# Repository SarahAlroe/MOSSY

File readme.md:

_Work in progress_  
# MOSSY  
A collection sound synthesis and processing electronics and software. 
_Work in progress_

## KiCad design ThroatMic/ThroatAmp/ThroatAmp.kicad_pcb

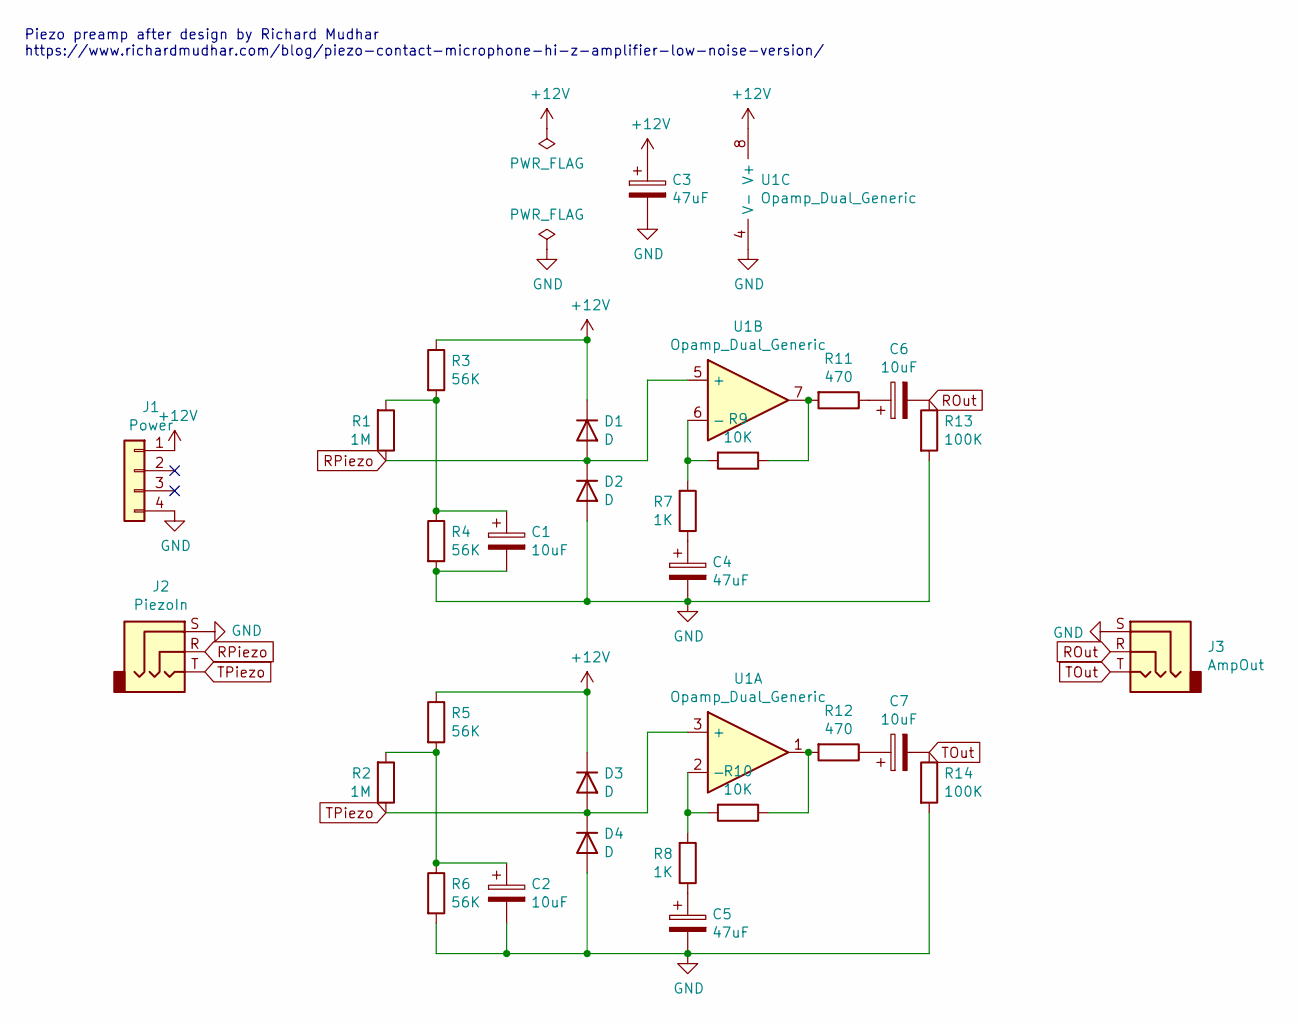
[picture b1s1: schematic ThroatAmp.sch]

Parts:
C1, C2, C6, C7: 10uF; C_Disc_D4.7mm_W2.5mm_P5.00mm
C3, C4, C5: 47uF; C_Disc_D4.7mm_W2.5mm_P5.00mm
D1, D2, D3, D4: D; D_5W_P10.16mm_Horizontal
J1: Power; PinHeader_1x04_P2.54mm_Horizontal
J2: PiezoIn; Jack_3.5mm_CUI_SJ1-3533NG_Horizontal
J3: AmpOut; Jack_3.5mm_CUI_SJ1-3533NG_Horizontal
R1, R2: 1M; R_Axial_DIN0207_L6.3mm_D2.5mm_P10.16mm_Horizontal
R3, R4, R5, R6: 56K; R_Axial_DIN0207_L6.3mm_D2.5mm_P10.16mm_Horizontal
R7, R8: 1K; R_Axial_DIN0207_L6.3mm_D2.5mm_P10.16mm_Horizontal
R9, R10: 10K; R_Axial_DIN0207_L6.3mm_D2.5mm_P10.16mm_Horizontal
R11, R12: 470; R_Axial_DIN0207_L6.3mm_D2.5mm_P10.16mm_Horizontal
R13, R14: 100K; R_Axial_DIN0207_L6.3mm_D2.5mm_P10.16mm_Horizontal
U1: Opamp_Dual_Generic; DIP-8_W7.62mm_LongPads

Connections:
+12V: C3.1, D1.1 (K), D3.1 (K), J1.1, R3.1, R5.1, U1.8 (V+)
GND: C1.2, C2.2, C3.2, C4.2, C5.2, D2.2 (A), D4.2 (A), J1.4, J2.S, J3.S, R4.2, R6.2, R13.2, R14.2, U1.4 (V-)
unnamed: C1.1, R1.2, R3.2, R4.1
unnamed: C2.1, R2.2, R5.2, R6.1
unnamed: C4.1, R7.1
unnamed: C5.1, R8.1
unnamed: C6.1, R11.1
unnamed: C7.1, R12.1
unnamed: R7.2, R9.2, U1.6 (-)
unnamed: R10.1, R12.2, U1.1
unnamed: R8.2, R10.2, U1.2 (-)
unnamed: R9.1, R11.2, U1.7
ROut: C6.2, J3.R, R13.1
RPiezo: D1.2 (A), D2.1 (K), J2.R, R1.1, U1.5 (+)
TOut: C7.2, J3.T, R14.1
TPiezo: D3.2 (A), D4.1 (K), J2.T, R2.1, U1.3 (+)

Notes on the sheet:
Piezo preamp after design by Richard Mudhar https://www.richardmudhar.com/blog/piezo-contact-microphone-hi-z-amplifier-low-noise-version/

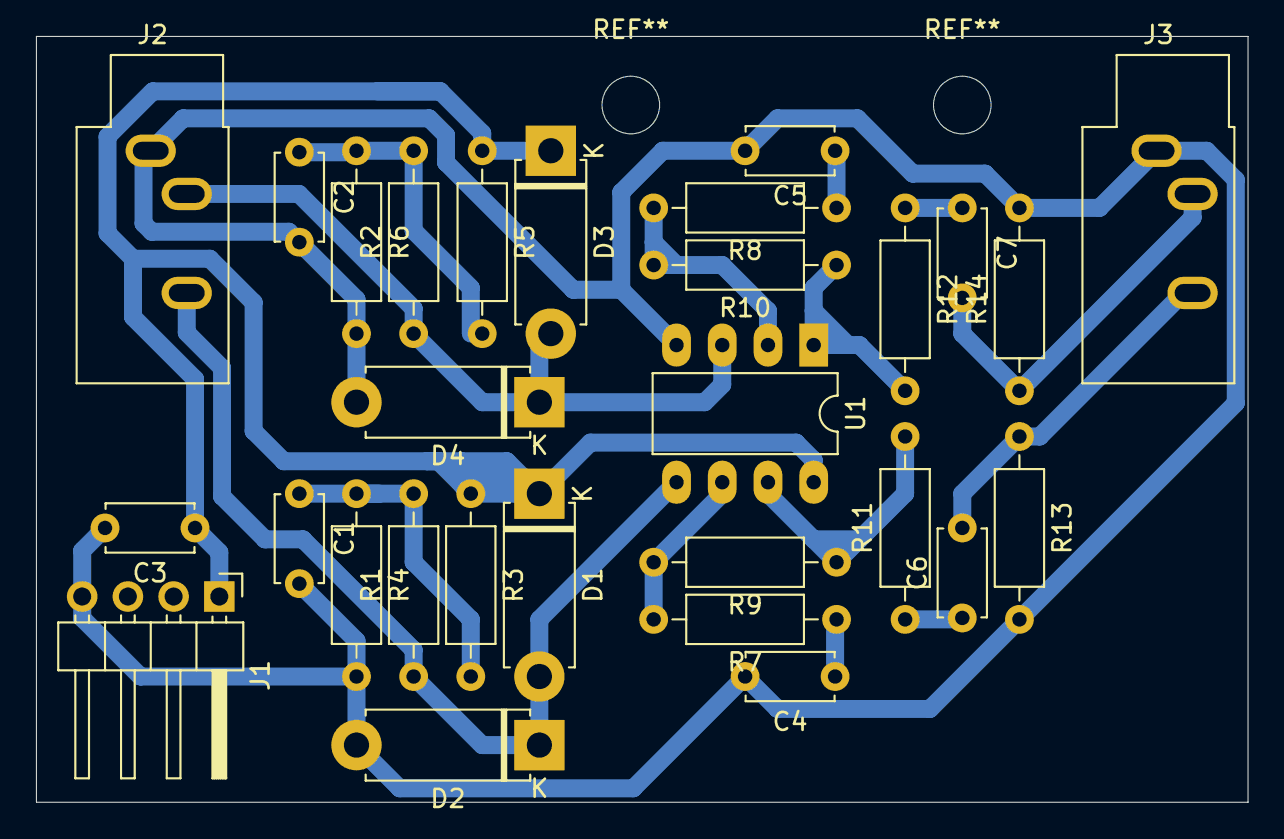
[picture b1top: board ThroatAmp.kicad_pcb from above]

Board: 2 copper layers, 67.3 x 42.5 mm, 29 parts (0 on the bottom side), 16 nets.

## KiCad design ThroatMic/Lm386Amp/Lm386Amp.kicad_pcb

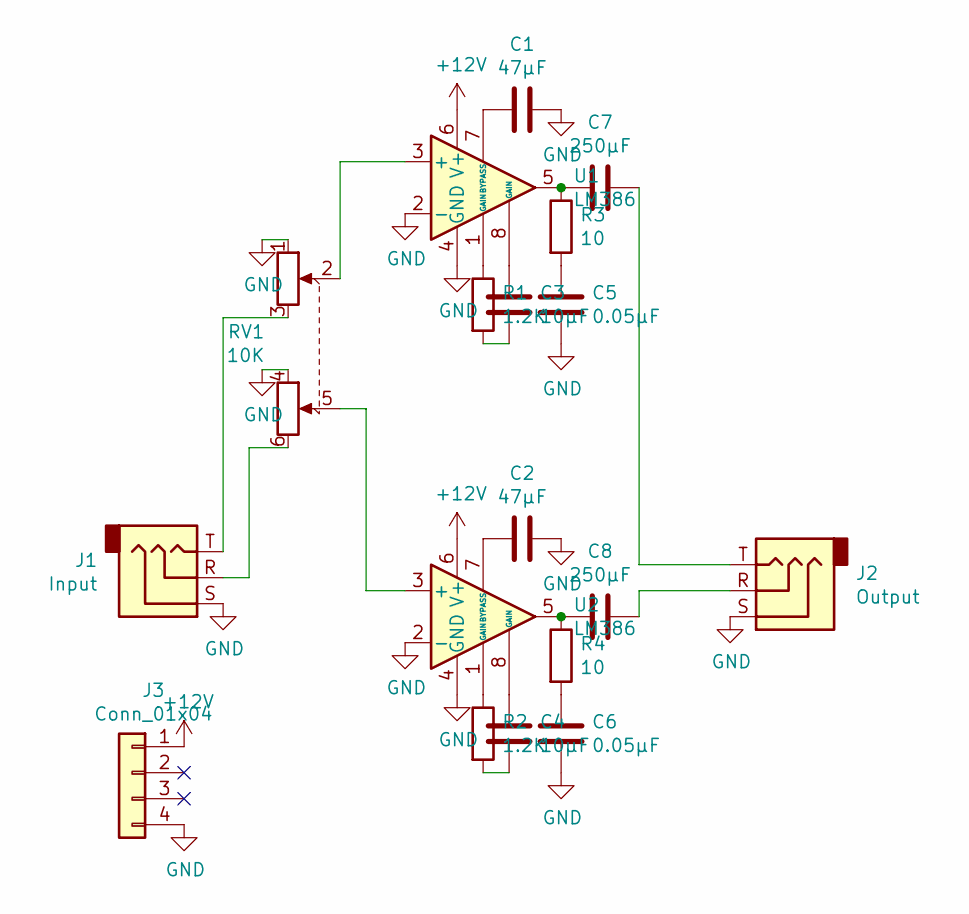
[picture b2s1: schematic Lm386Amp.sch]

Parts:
C1, C2: 47µF; C_Disc_D4.7mm_W2.5mm_P5.00mm
C3, C4: 10µF; C_Disc_D4.7mm_W2.5mm_P5.00mm
C5, C6: 0.05µF; C_Disc_D4.7mm_W2.5mm_P5.00mm
C7, C8: 250µF; C_Disc_D4.7mm_W2.5mm_P5.00mm
J1: Input; Jack_3.5mm_CUI_SJ1-3533NG_Horizontal
J2: Output; Jack_3.5mm_CUI_SJ1-3533NG_Horizontal
J3: Conn_01x04; PinHeader_1x04_P2.54mm_Horizontal
R1, R2: 1.2K; R_Axial_DIN0207_L6.3mm_D2.5mm_P10.16mm_Horizontal
R3, R4: 10; R_Axial_DIN0207_L6.3mm_D2.5mm_P10.16mm_Horizontal
RV1: 10K; Potentiometer_Alps_RK163_Dual_Horizontal
U1, U2: LM386; DIP-8_W7.62mm_Socket_LongPads

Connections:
+12V: J3.1, U1.6 (V+), U2.6 (V+)
GND: C1.2, C2.2, C5.2, C6.2, J1.S, J2.S, J3.4, RV1.1, RV1.4, U1.2 (-), U1.4 (GND), U2.2 (-), U2.4 (GND)
unnamed: C1.1, U1.7 (BYPASS)
unnamed: C2.1, U2.7 (BYPASS)
unnamed: C3.1, U1.8 (GAIN)
unnamed: C3.2, R1.2
unnamed: C4.1, U2.8 (GAIN)
unnamed: C4.2, R2.2
unnamed: C5.1, R3.2
unnamed: C6.1, R4.2
unnamed: C7.1, J2.T
unnamed: C7.2, R3.1, U1.5
unnamed: C8.1, J2.R
unnamed: C8.2, R4.1, U2.5
unnamed: J1.R, RV1.6
unnamed: J1.T, RV1.3
unnamed: R1.1, U1.1 (GAIN)
unnamed: R2.1, U2.1 (GAIN)
unnamed: RV1.2, U1.3 (+)
unnamed: RV1.5, U2.3 (+)

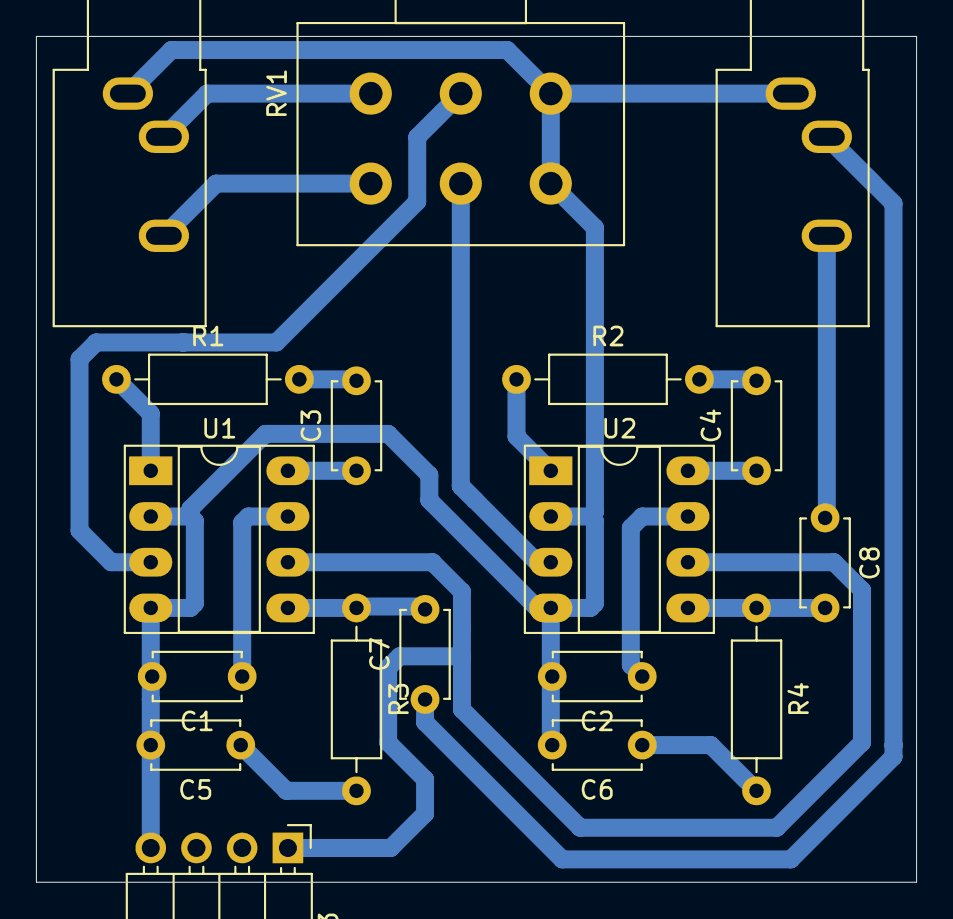
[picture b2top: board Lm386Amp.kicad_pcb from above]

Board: 2 copper layers, 48.9 x 47.0 mm, 18 parts (0 on the bottom side), 20 nets.

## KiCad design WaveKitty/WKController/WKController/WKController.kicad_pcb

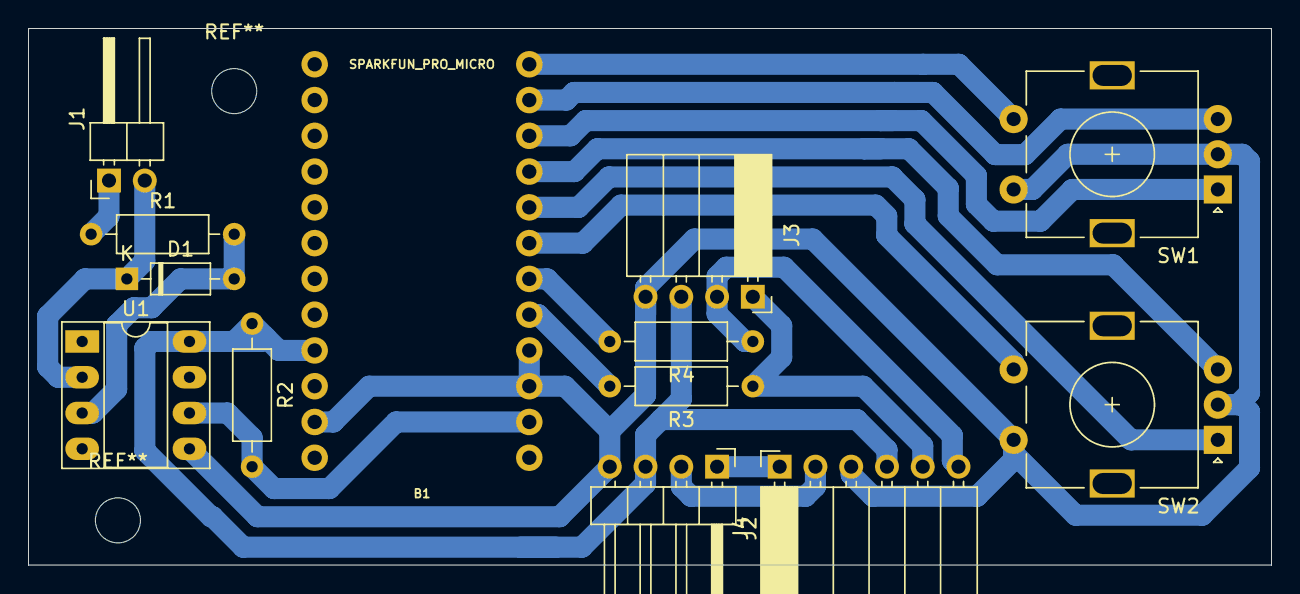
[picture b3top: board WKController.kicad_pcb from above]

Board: 2 copper layers, 88.3 x 38.1 mm, 13 parts (0 on the bottom side), 18 nets.

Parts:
B1: SPARKFUN_PRO_MICRO
D1: 1N914; D_DO-35_SOD27_P7.62mm_Horizontal
J1: MIDI; PinHeader_1x02_P2.54mm_Horizontal
J2: Power; PinHeader_1x04_P2.54mm_Horizontal
J3: SSD1306; PinSocket_1x04_P2.54mm_Horizontal
J4: VoiceCon; PinSocket_1x06_P2.54mm_Horizontal
R1: 220; R_Axial_DIN0207_L6.3mm_D2.5mm_P10.16mm_Horizontal
R2: 270; R_Axial_DIN0207_L6.3mm_D2.5mm_P10.16mm_Horizontal
R3, R4: 0; R_Axial_DIN0207_L6.3mm_D2.5mm_P10.16mm_Horizontal
SW1: L_ENC; RotaryEncoder_Alps_EC11E-Switch_Vertical_H20mm
SW2: R_ENC; RotaryEncoder_Alps_EC11E-Switch_Vertical_H20mm
U1: 6N138; DIP-8_W7.62mm_Socket_LongPads

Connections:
+5V: B1.21, J2.3, J3.3, J4.4, R2.1, U1.8
+12V: J2.1, J4.1
-12V: J2.2, J4.2
GND: B1.3, B1.4, B1.23, J2.4, J3.4, J4.3, SW1.C, SW1.S2, SW2.C, SW2.S2, U1.5
L_ENC_A: B1.10, SW1.A
L_ENC_B: B1.11, SW1.B
L_ENC_S: B1.12, SW1.S1
unnamed: B1.5, R3.2
unnamed: B1.6, R4.2
unnamed: D1.1, J1.2, U1.2
unnamed: D1.2, R1.2, U1.3
unnamed: J1.1, R1.1
RXI: B1.2, R2.2, U1.6
R_ENC_A: B1.8, SW2.A
R_ENC_B: B1.9, SW2.B
R_ENC_S: B1.7, SW2.S1
SCL: J3.2, J4.6, R4.1
SDA: J3.1, J4.5, R3.1

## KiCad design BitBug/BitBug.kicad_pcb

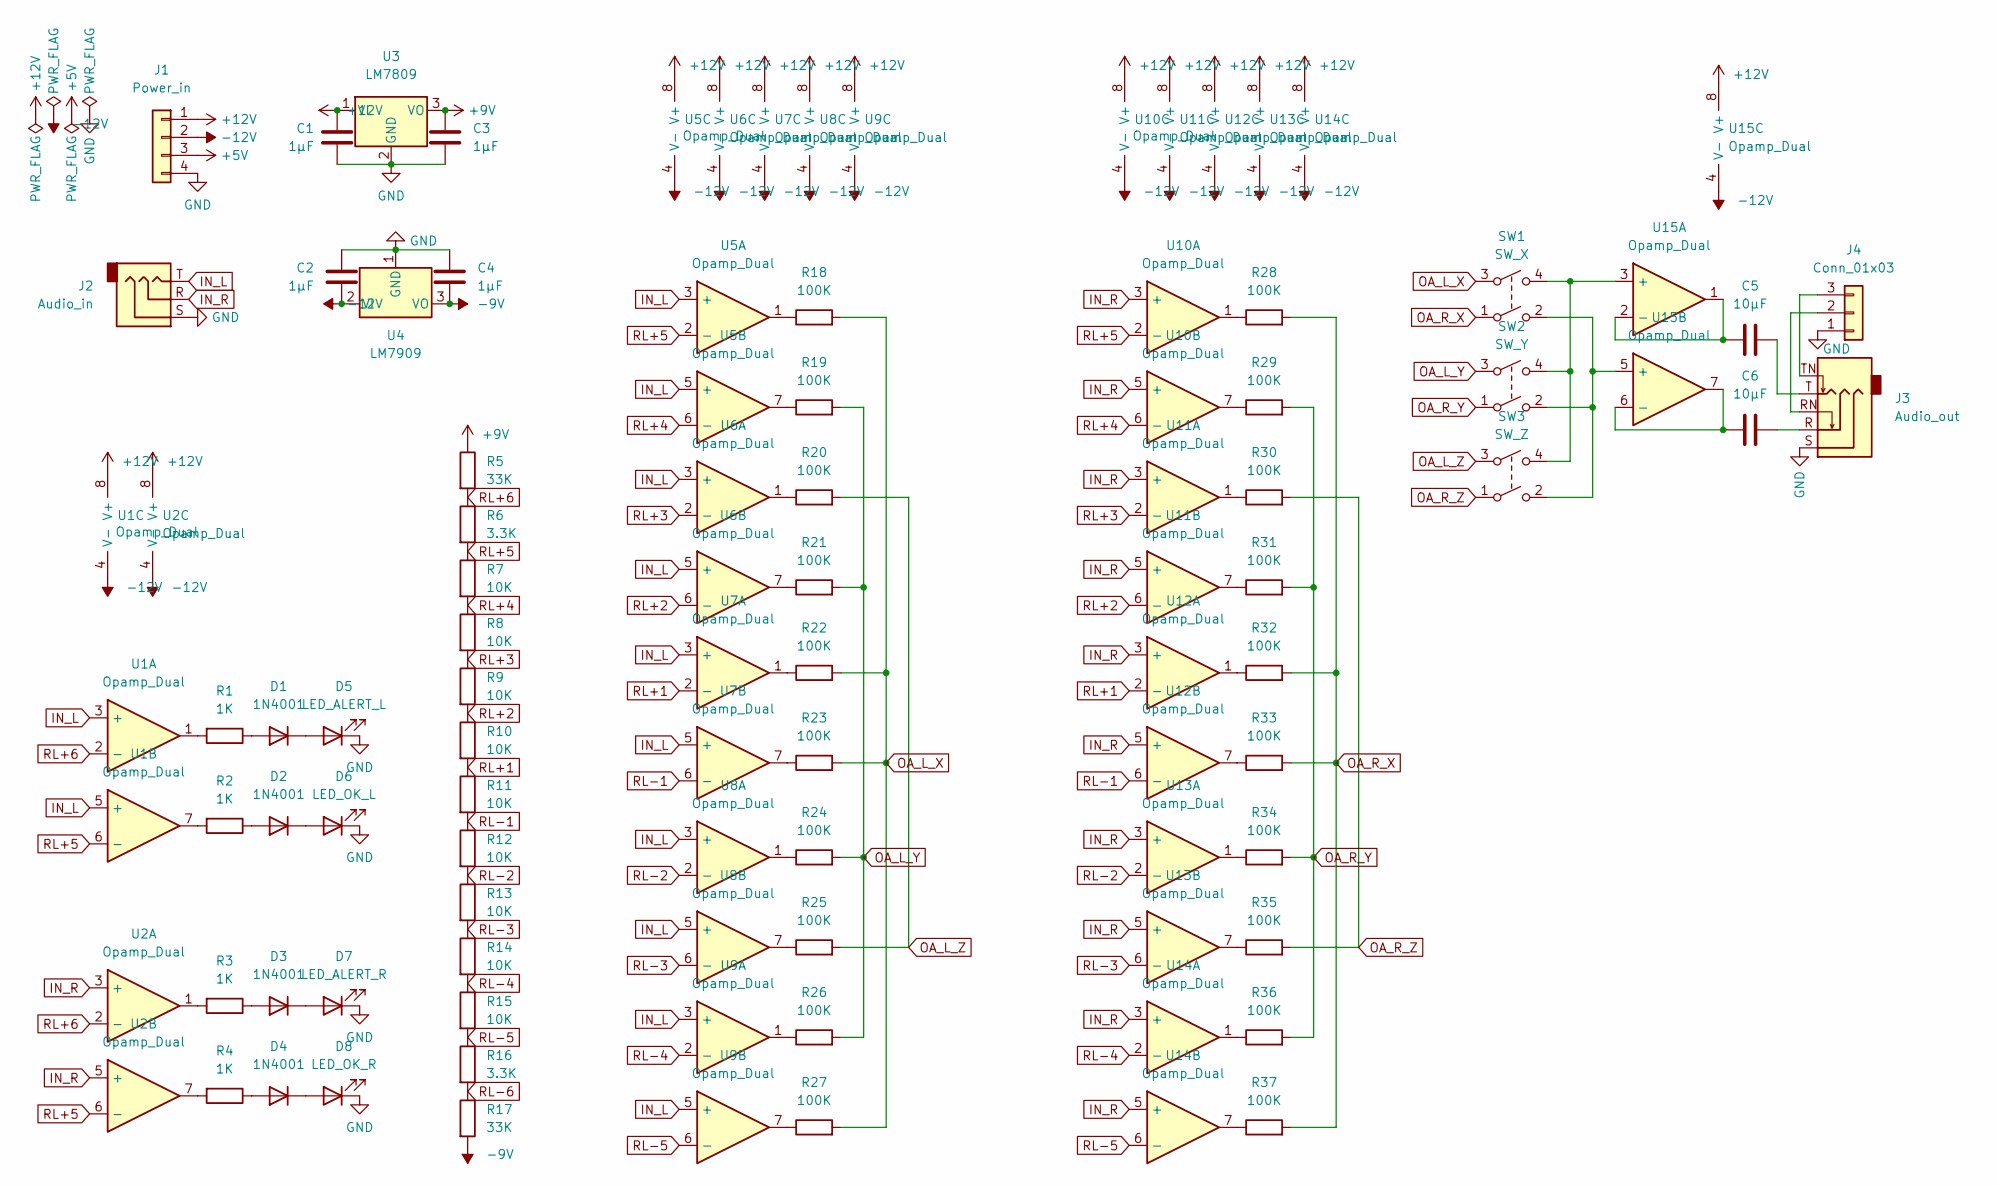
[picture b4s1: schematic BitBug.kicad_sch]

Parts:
C1, C2, C3, C4: 1µF; C_Disc_D4.7mm_W2.5mm_P5.00mm
C5, C6: 10µF; C_Disc_D4.7mm_W2.5mm_P5.00mm
D1, D2, D3, D4: 1N4001; D_DO-41_SOD81_P10.16mm_Horizontal
D5: LED_ALERT_L; LED_D5.0mm
D6: LED_OK_L; LED_D5.0mm
D7: LED_ALERT_R; LED_D5.0mm
D8: LED_OK_R; LED_D5.0mm
J1: Power_in; PinHeader_1x04_P2.54mm_Horizontal
J2: Audio_in; Jack_3.5mm_Ledino_KB3SPRS_Horizontal
J3: Audio_out; Jack_3.5mm_Ledino_KB3SPRS_Horizontal
J4: Conn_01x03; PinSocket_1x03_P2.54mm_Vertical
R1, R2, R3, R4: 1K; R_Axial_DIN0207_L6.3mm_D2.5mm_P7.62mm_Horizontal
R5, R17: 33K; R_Axial_DIN0207_L6.3mm_D2.5mm_P7.62mm_Horizontal
R6, R16: 3.3K; R_Axial_DIN0207_L6.3mm_D2.5mm_P7.62mm_Horizontal
R7, R8, R9, R10, R11, R12, R13, R14, R15: 10K; R_Axial_DIN0207_L6.3mm_D2.5mm_P7.62mm_Horizontal
R18, R19, R20, R21, R22, R23, R24, R25, R26, R27, R28, R29, R30, R31, R32, R33, R34, R35, R36, R37: 100K; R_Axial_DIN0207_L6.3mm_D2.5mm_P7.62mm_Horizontal
SW1: SW_X; PinSocket_1x04_P2.54mm_Vertical
SW2: SW_Y; PinSocket_1x04_P2.54mm_Vertical
SW3: SW_Z; PinSocket_1x04_P2.54mm_Vertical
U1, U2, U5, U6, U7, U8, U9, U10, U11, U12, U13, U14, U15: Opamp_Dual; DIP-8_W7.62mm_LongPads
U3: LM7809; TO-220-3_Vertical
U4: LM7909; TO-220-3_Vertical

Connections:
+5V: J1.3
+9V: C3.1, R5.1, U3.3 (VO)
+12V: C1.2, J1.1, U1.8 (V+), U2.8 (V+), U3.1 (VI), U5.8 (V+), U6.8 (V+), U7.8 (V+), U8.8 (V+), U9.8 (V+), U10.8 (V+), U11.8 (V+), U12.8 (V+), U13.8 (V+), U14.8 (V+), U15.8 (V+)
-9V: C4.2, R17.2, U4.3 (VO)
-12V: C2.1, J1.2, U1.4 (V-), U2.4 (V-), U4.2 (VI), U5.4 (V-), U6.4 (V-), U7.4 (V-), U8.4 (V-), U9.4 (V-), U10.4 (V-), U11.4 (V-), U12.4 (V-), U13.4 (V-), U14.4 (V-), U15.4 (V-)
GND: C1.1, C2.2, C3.2, C4.1, D5.1 (K), D6.1 (K), D7.1 (K), D8.1 (K), J1.4, J2.S, J3.S, J4.1, U3.2 (GND), U4.1 (GND)
IN_L: J2.T, U1.3 (+), U1.5 (+), U5.3 (+), U5.5 (+), U6.3 (+), U6.5 (+), U7.3 (+), U7.5 (+), U8.3 (+), U8.5 (+), U9.3 (+), U9.5 (+)
IN_R: J2.R, U2.3 (+), U2.5 (+), U10.3 (+), U10.5 (+), U11.3 (+), U11.5 (+), U12.3 (+), U12.5 (+), U13.3 (+), U13.5 (+), U14.3 (+), U14.5 (+)
unnamed: C5.1, U15.1, U15.2 (-)
unnamed: C5.2, J3.T
unnamed: C6.1, U15.6 (-), U15.7
unnamed: C6.2, J3.R
unnamed: D1.1 (K), D5.2 (A)
unnamed: D1.2 (A), R1.1
unnamed: D2.1 (K), D6.2 (A)
unnamed: D2.2 (A), R2.1
unnamed: D3.1 (K), D7.2 (A)
unnamed: D3.2 (A), R3.1
unnamed: D4.1 (K), D8.2 (A)
unnamed: D4.2 (A), R4.1
unnamed: J3.RN, J4.2
unnamed: J3.TN, J4.3
unnamed: R1.2, U1.1
unnamed: R2.2, U1.7
unnamed: R3.2, U2.1
unnamed: R4.2, U2.7
unnamed: R18.1, U5.1
unnamed: R19.1, U5.7
unnamed: R20.1, U6.1
unnamed: R21.1, U6.7
unnamed: R22.1, U7.1
unnamed: R23.1, U7.7
unnamed: R24.1, U8.1
unnamed: R25.1, U8.7
unnamed: R26.1, U9.1
unnamed: R27.1, U9.7
unnamed: R28.1, U10.1
unnamed: R29.1, U10.7
unnamed: R30.1, U11.1
unnamed: R31.1, U11.7
unnamed: R32.1, U12.1
unnamed: R33.1, U12.7
unnamed: R34.1, U13.1
unnamed: R35.1, U13.7
unnamed: R36.1, U14.1
unnamed: R37.1, U14.7
unnamed: SW1.2, SW2.2, SW3.2, U15.5 (+)
unnamed: SW1.4, SW2.4, SW3.4, U15.3 (+)
OA_L_X: R18.2, R22.2, R23.2, R27.2, SW1.3
OA_L_Y: R19.2, R21.2, R24.2, R26.2, SW2.3
OA_L_Z: R20.2, R25.2, SW3.3
OA_R_X: R28.2, R32.2, R33.2, R37.2, SW1.1
OA_R_Y: R29.2, R31.2, R34.2, R36.2, SW2.1
OA_R_Z: R30.2, R35.2, SW3.1
RL+1: R10.2, R11.1, U7.2 (-), U12.2 (-)
RL+2: R9.2, R10.1, U6.6 (-), U11.6 (-)
RL+3: R8.2, R9.1, U6.2 (-), U11.2 (-)
RL+4: R7.2, R8.1, U5.6 (-), U10.6 (-)
RL+5: R6.2, R7.1, U1.6 (-), U2.6 (-), U5.2 (-), U10.2 (-)
RL+6: R5.2, R6.1, U1.2 (-), U2.2 (-)
RL-1: R11.2, R12.1, U7.6 (-), U12.6 (-)
RL-2: R12.2, R13.1, U8.2 (-), U13.2 (-)
RL-3: R13.2, R14.1, U8.6 (-), U13.6 (-)
RL-4: R14.2, R15.1, U9.2 (-), U14.2 (-)
RL-5: R15.2, R16.1, U9.6 (-), U14.6 (-)
RL-6: R16.2, R17.1

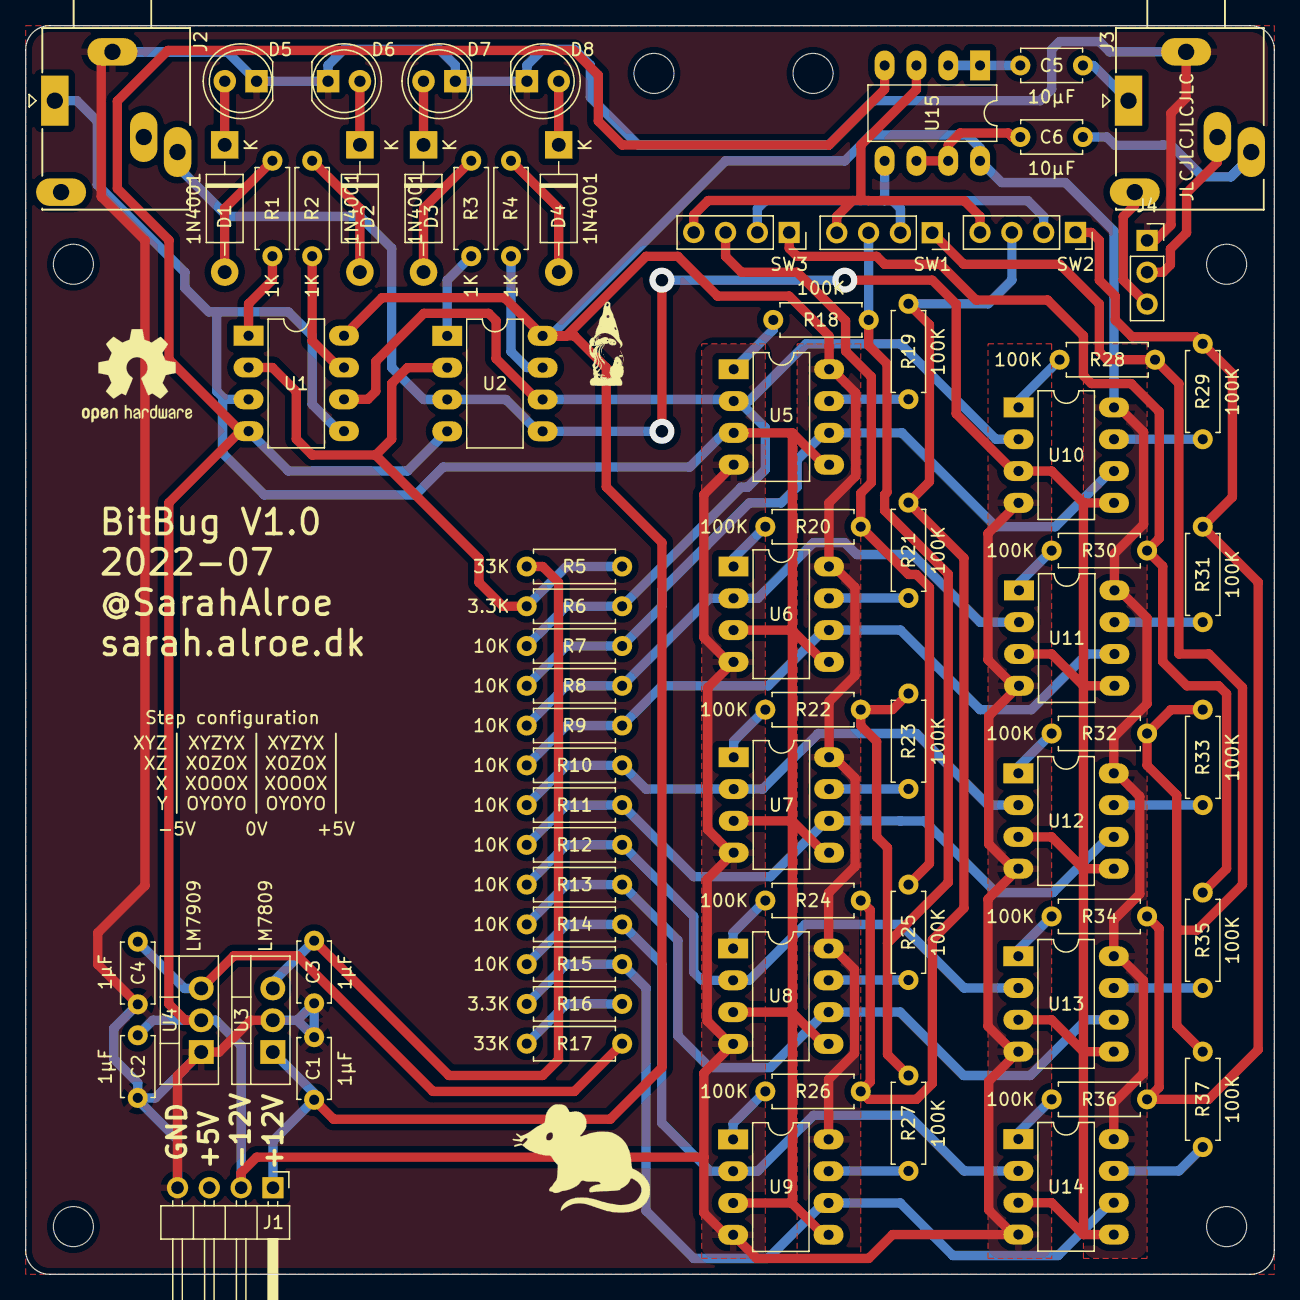
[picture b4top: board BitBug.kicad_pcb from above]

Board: 2 copper layers, 99.7 x 99.7 mm, 73 parts (0 on the bottom side), 65 nets.

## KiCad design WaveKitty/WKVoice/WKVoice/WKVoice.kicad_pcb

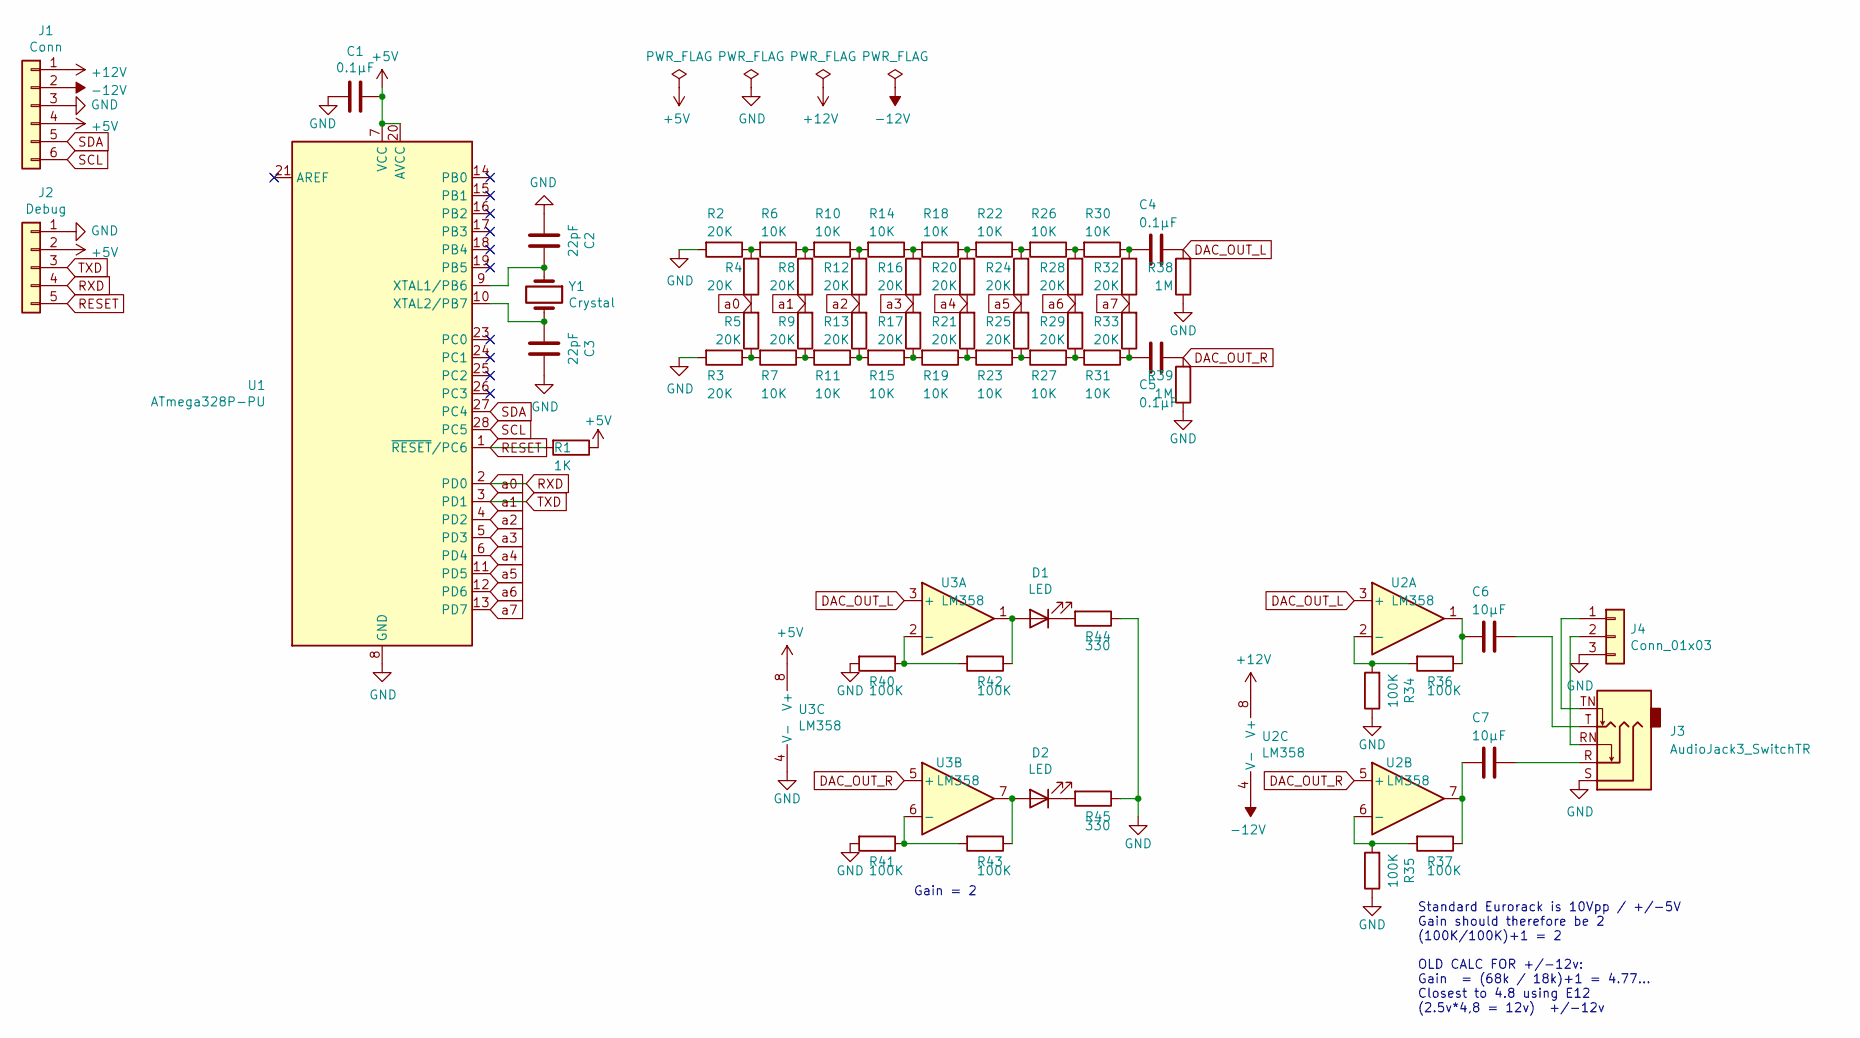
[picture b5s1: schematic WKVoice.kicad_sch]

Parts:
C1, C4, C5: 0.1µF; C_Disc_D4.7mm_W2.5mm_P5.00mm
C2, C3: 22pF; C_Disc_D4.7mm_W2.5mm_P5.00mm
C6, C7: 10µF; C_Disc_D4.7mm_W2.5mm_P5.00mm
D1, D2: LED; LED_D5.0mm_Horizontal_O1.27mm_Z15.0mm
J1: Conn; PinHeader_1x06_P2.54mm_Horizontal
J2: Debug; PinSocket_1x05_P2.54mm_Vertical
J3: AudioJack3_SwitchTR; Jack_3.5mm_Ledino_KB3SPRS_Horizontal
J4: Conn_01x03; PinSocket_1x03_P2.54mm_Vertical
R1: 1K; R_Axial_DIN0207_L6.3mm_D2.5mm_P10.16mm_Horizontal
R2, R3, R4, R5, R8, R9, R12, R13, R16, R17, R20, R21, R24, R25, R28, R29, R32, R33: 20K; R_Axial_DIN0207_L6.3mm_D2.5mm_P10.16mm_Horizontal
R6, R7, R10, R11, R14, R15, R18, R19, R22, R23, R26, R27, R30, R31: 10K; R_Axial_DIN0207_L6.3mm_D2.5mm_P10.16mm_Horizontal
R34, R35, R36, R37, R40, R41, R42, R43: 100K; R_Axial_DIN0207_L6.3mm_D2.5mm_P10.16mm_Horizontal
R38, R39: 1M; R_Axial_DIN0207_L6.3mm_D2.5mm_P10.16mm_Horizontal
R44, R45: 330; R_Axial_DIN0207_L6.3mm_D2.5mm_P10.16mm_Horizontal
U1: ATmega328P-PU; DIP-28_W7.62mm
U2, U3: LM358; DIP-8_W7.62mm_LongPads
Y1: Crystal; Crystal_HC49-U_Vertical

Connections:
+5V: C1.1, J1.4, J2.2, R1.1, U1.7 (VCC), U1.20 (AVCC), U3.8 (V+)
+12V: J1.1, U2.8 (V+)
-12V: J1.2, U2.4 (V-)
DAC_OUT_L: C4.2, R38.2, U2.3 (+), U3.3 (+)
DAC_OUT_R: C5.2, R39.2, U2.5 (+), U3.5 (+)
GND: C1.2, C2.2, C3.1, J1.3, J2.1, J3.S, J4.3, R2.2, R3.2, R34.1, R35.1, R38.1, R39.1, R40.2, R41.2, R44.1, R45.1, U1.8 (GND), U1.22 (GND), U3.4 (V-)
unnamed: C2.1, U1.9 (XTAL1/PB6), Y1.1
unnamed: C3.2, U1.10 (XTAL2/PB7), Y1.2
unnamed: C4.1, R30.1, R32.2
unnamed: C5.1, R31.1, R33.1
unnamed: C6.1, R36.1, U2.1
unnamed: C7.1, R37.1, U2.7
unnamed: D1.1 (K), R44.2
unnamed: D1.2 (A), R42.1, U3.1
unnamed: D2.1 (K), R45.2
unnamed: D2.2 (A), R43.1, U3.7
unnamed: C7.2, J3.R
unnamed: C6.2, J3.T
unnamed: J3.TN, J4.1
unnamed: J3.RN, J4.2
unnamed: R2.1, R4.2, R6.2
unnamed: R3.1, R5.1, R7.2
unnamed: R10.1, R12.2, R14.2
unnamed: R6.1, R8.2, R10.2
unnamed: R11.1, R13.1, R15.2
unnamed: R7.1, R9.1, R11.2
unnamed: R14.1, R16.2, R18.2
unnamed: R15.1, R17.1, R19.2
unnamed: R18.1, R20.2, R22.2
unnamed: R19.1, R21.1, R23.2
unnamed: R22.1, R24.2, R26.2
unnamed: R23.1, R25.1, R27.2
unnamed: R26.1, R28.2, R30.2
unnamed: R27.1, R29.1, R31.2
unnamed: R34.2, R36.2, U2.2 (-)
unnamed: R35.2, R37.2, U2.6 (-)
unnamed: R40.1, R42.2, U3.2 (-)
unnamed: R41.1, R43.2, U3.6 (-)
RESET: J2.5, R1.2, U1.1 (~RESET/PC6)
RXD: J2.4, R4.1, R5.2, U1.2 (PD0)
SCL: J1.6, U1.28 (PC5)
SDA: J1.5, U1.27 (PC4)
TXD: J2.3, R8.1, R9.2, U1.3 (PD1)
a2: R12.1, R13.2, U1.4 (PD2)
a3: R16.1, R17.2, U1.5 (PD3)
a4: R20.1, R21.2, U1.6 (PD4)
a5: R24.1, R25.2, U1.11 (PD5)
a6: R28.1, R29.2, U1.12 (PD6)
a7: R32.1, R33.2, U1.13 (PD7)

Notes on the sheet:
OLD CALC FOR +/-12v: Gain = (68k / 18k)+1 = 4.77... Closest to 4.8 using E12 (2.5v*4,8 = 12v) ~{} +/-12v
Gain = 2
Standard Eurorack is 10Vpp / +/-5V Gain should therefore be 2 (100K/100K)+1 = 2

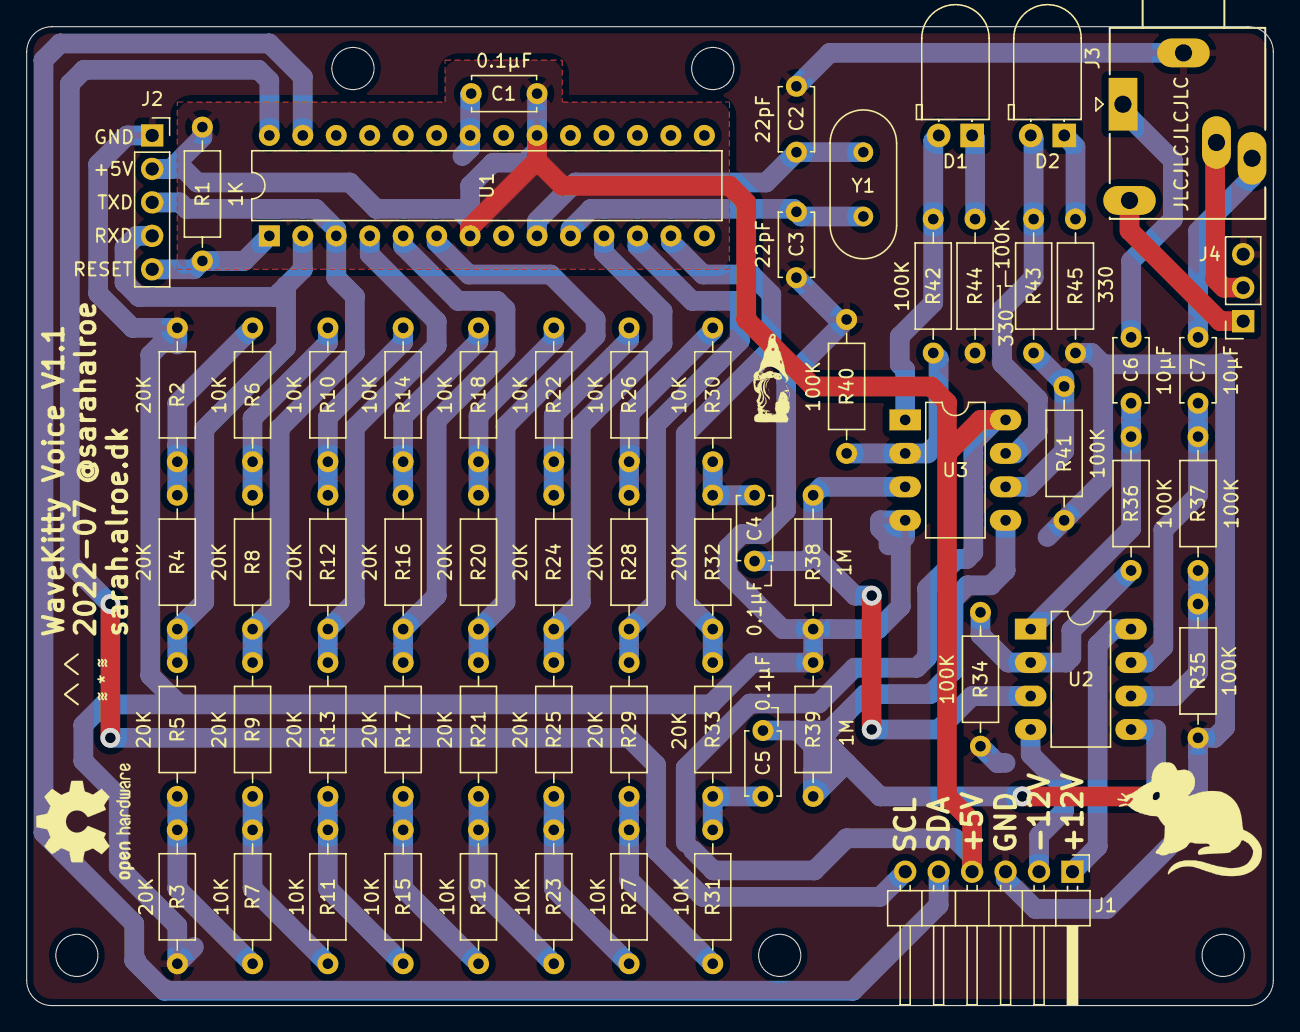
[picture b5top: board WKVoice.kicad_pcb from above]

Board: 2 copper layers, 94.6 x 74.3 mm, 62 parts (0 on the bottom side), 49 nets.

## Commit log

2019-03-05 Init
2021-08-10 Created single sided WaveKitty PCBs
2022-08-26 Initial work on BitBug
2022-08-26 Various things
2022-08-26 ThroatMicrphone panels
